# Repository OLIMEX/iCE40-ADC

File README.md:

# iCE40-ADC
Extension module for iCE40HX1K-EVB or iCE40HX8K-EVB.

Adds fast Analog-Digital-Converter (ADC) functionality to the main board.

You can effectively use up to 4 x iCE40-ADC with a single EVB board (or up to 2 x iCE40-ADC 
when you have iCE40-IO connected to the same bus).

You can use the exported PDFs to access the schematic or the bill of materials. 

We used the latest KiCad night builds to create the design. Please use a new version KiCad to open it. 

License information should be found in LICENSE.txt

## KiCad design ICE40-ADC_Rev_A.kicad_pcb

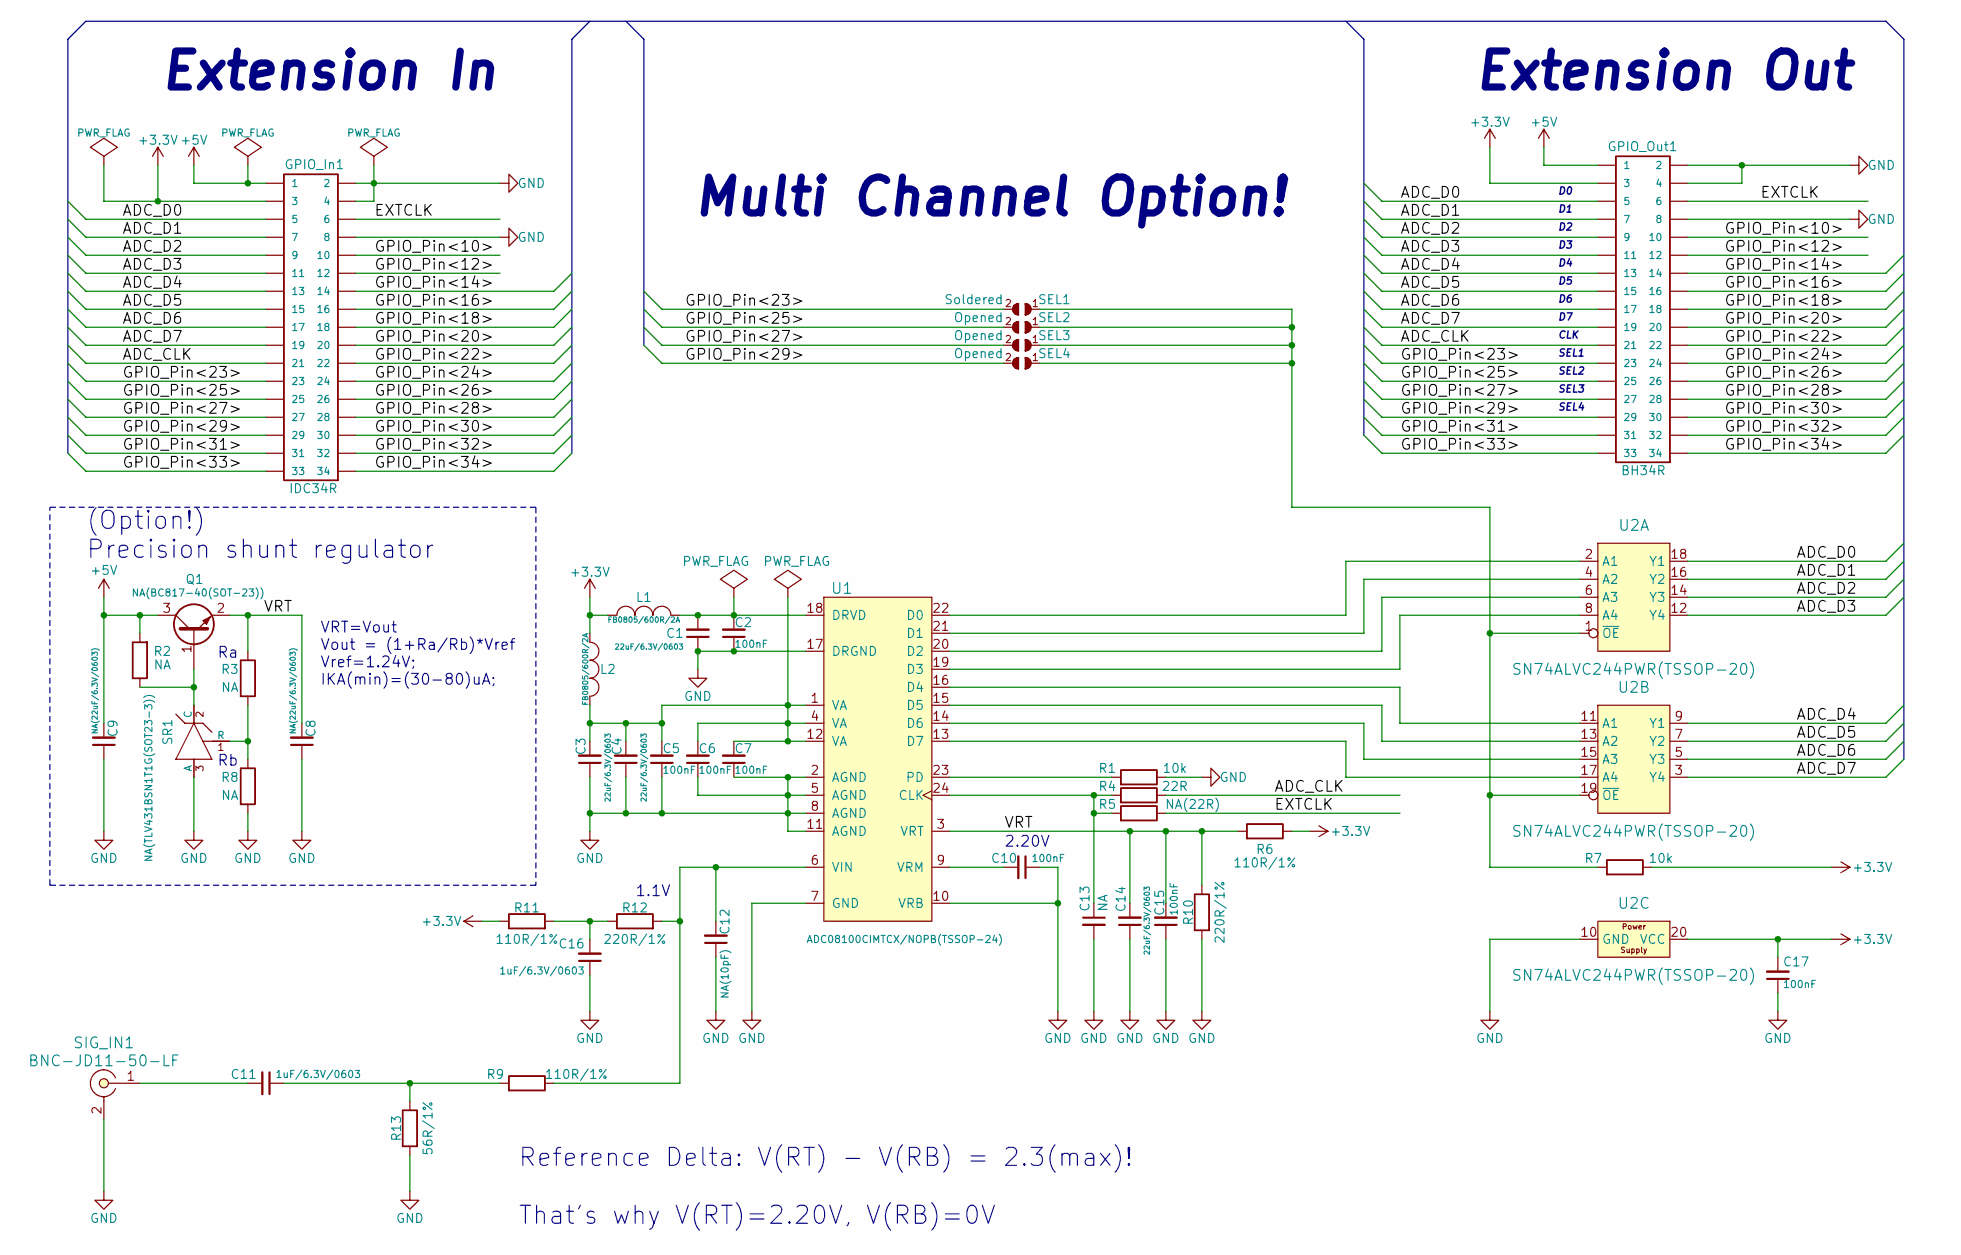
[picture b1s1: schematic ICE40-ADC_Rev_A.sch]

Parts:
C1, C3, C4, C14: 22uF/6.3V/0603; C_0603_5MIL_DWS
C2, C5, C6, C7, C10, C15, C17: 100nF; C_0402_5MIL_DWS
C8, C9: NA(22uF/6.3V/0603); C_0603_5MIL_DWS
C11, C16: 1uF/6.3V/0603; C_0603_5MIL_DWS
C12: NA(10pF); C_0402_5MIL_DWS
C13: NA; C_0402_5MIL_DWS
GPIO_In1: IDC34R; IDC34R_PCB
GPIO_Out1: BH34R
L1, L2: FB0805/600R/2A; L_0805_5MIL_DWS
Q1: NA(BC817-40(SOT-23)); SOT23
R1, R7: 10k; R_0402_5MIL_DWS
R2, R3, R8: NA; R_0402_5MIL_DWS
R4: 22R; R_0402_5MIL_DWS
R5: NA(22R); R_0402_5MIL_DWS
R6, R9, R11: 110R/1%; R_0402_5MIL_DWS
R10, R12: 220R/1%; R_0402_5MIL_DWS
R13: 56R/1%; R_0402_5MIL_DWS
SEL1: Soldered; SJ
SEL2, SEL3, SEL4: Opened; SJ
SIG_IN1: BNC-JD11-50-LF; BNC-JD11-50-LF_1-IN_2-GND
SR1: NA(TLV431BSN1T1G(SOT23-3)); SOT-23
U1: ADC08100CIMTCX/NOPB(TSSOP-24); TSSOP-24_Pitch-0.65mm_7.80x6.40x1.20mm
U2: SN74ALVC244PWR(TSSOP-20); TSSOP20_Pitch-0.65mm_6.6x4.5x1.2mm

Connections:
+3V3: C17.2, GPIO_In1.3, GPIO_Out1.3, L1.2, L2.2, R6.1, R7.1, R11.1, U2.20 (VCC)
+5V: C9.2, GPIO_In1.1, GPIO_Out1.1, Q1.3 (C), R2.2
/ADC_CLK: GPIO_In1.21, GPIO_Out1.21, R4.1
/ADC_D0: GPIO_In1.5, GPIO_Out1.5, U2.18 (Y1)
/ADC_D1: GPIO_In1.7, GPIO_Out1.7, U2.16 (Y2)
/ADC_D2: GPIO_In1.9, GPIO_Out1.9, U2.14 (Y3)
/ADC_D3: GPIO_In1.11, GPIO_Out1.11, U2.12 (Y4)
/ADC_D4: GPIO_In1.13, GPIO_Out1.13, U2.9 (Y1)
/ADC_D5: GPIO_In1.15, GPIO_Out1.15, U2.7 (Y2)
/ADC_D6: GPIO_In1.17, GPIO_Out1.17, U2.5 (Y3)
/ADC_D7: GPIO_In1.19, GPIO_Out1.19, U2.3 (Y4)
/EXTCLK: GPIO_In1.6, GPIO_Out1.6, R5.1
/GPIO_Pin<10>: GPIO_In1.10, GPIO_Out1.10
/GPIO_Pin<12>: GPIO_In1.12, GPIO_Out1.12
/GPIO_Pin<14>: GPIO_In1.14, GPIO_Out1.14
/GPIO_Pin<16>: GPIO_In1.16, GPIO_Out1.16
/GPIO_Pin<18>: GPIO_In1.18, GPIO_Out1.18
/GPIO_Pin<20>: GPIO_In1.20, GPIO_Out1.20
/GPIO_Pin<22>: GPIO_In1.22, GPIO_Out1.22
/GPIO_Pin<23>: GPIO_In1.23, GPIO_Out1.23, SEL1.2
/GPIO_Pin<24>: GPIO_In1.24, GPIO_Out1.24
/GPIO_Pin<25>: GPIO_In1.25, GPIO_Out1.25, SEL2.2
/GPIO_Pin<26>: GPIO_In1.26, GPIO_Out1.26
/GPIO_Pin<27>: GPIO_In1.27, GPIO_Out1.27, SEL3.2
/GPIO_Pin<28>: GPIO_In1.28, GPIO_Out1.28
/GPIO_Pin<29>: GPIO_In1.29, GPIO_Out1.29, SEL4.2
/GPIO_Pin<30>: GPIO_In1.30, GPIO_Out1.30
/GPIO_Pin<31>: GPIO_In1.31, GPIO_Out1.31
/GPIO_Pin<32>: GPIO_In1.32, GPIO_Out1.32
/GPIO_Pin<33>: GPIO_In1.33, GPIO_Out1.33
/GPIO_Pin<34>: GPIO_In1.34, GPIO_Out1.34
/VRT: C8.2, C14.2, C15.2, Q1.2 (E), R3.1, R6.2, R10.1, U1.3 (VRT)
GND: C1.1, C2.1, C3.1, C4.1, C5.1, C6.1, C7.1, C8.1, C9.1, C10.1, C12.1, C13.2, C14.1, C15.1, C16.1, C17.1, GPIO_In1.2, GPIO_In1.4, GPIO_In1.8, GPIO_Out1.2, GPIO_Out1.4, GPIO_Out1.8, R1.1, R8.2, R10.2, R13.2, SIG_IN1.2, SR1.3 (A), U1.2 (AGND), U1.5 (AGND), U1.7 (GND), U1.8 (AGND), U1.10 (VRB), U1.11 (AGND), U1.17 (DRGND), U2.10 (GND)
unnamed: C1.2, C2.2, L1.1, U1.18 (DRVD)
unnamed: C3.2, C4.2, C5.2, C6.2, C7.2, L2.1, U1.1 (VA), U1.4 (VA), U1.12 (VA)
unnamed: C10.2, U1.9 (VRM)
unnamed: C11.1, R9.2, R13.1
unnamed: C11.2, SIG_IN1.1
unnamed: C12.2, R9.1, R12.2, U1.6 (VIN)
unnamed: C13.1, R4.2, R5.2, U1.24 (CLK)
unnamed: C16.2, R11.2, R12.1
unnamed: Q1.1 (B), R2.1, SR1.2 (C)
unnamed: R1.2, U1.23 (PD)
unnamed: R3.2, R8.1, SR1.1 (R)
unnamed: R7.2, SEL1.1, SEL2.1, SEL3.1, SEL4.1, U2.1 (~OE), U2.19 (~OE)
unnamed: U1.13 (D7), U2.17 (A4)
unnamed: U1.14 (D6), U2.15 (A3)
unnamed: U1.15 (D5), U2.13 (A2)
unnamed: U1.16 (D4), U2.11 (A1)
unnamed: U1.19 (D3), U2.8 (A4)
unnamed: U1.20 (D2), U2.6 (A3)
unnamed: U1.21 (D1), U2.4 (A2)
unnamed: U1.22 (D0), U2.2 (A1)

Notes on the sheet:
Extension Out
Extension In
VRT=Vout Vout = (1+Ra/Rb)*Vref Vref=1.24V; IKA(min)=(30-80)uA;
2.20V
1.1V
Reference Delta: V(RT) - V(RB) = 2.3(max)! That's why V(RT)=2.20V, V(RB)=0V
(Option!) Precision shunt regulator
Multi Channel Option!
CLK
SEL1
SEL2
SEL3
SEL4

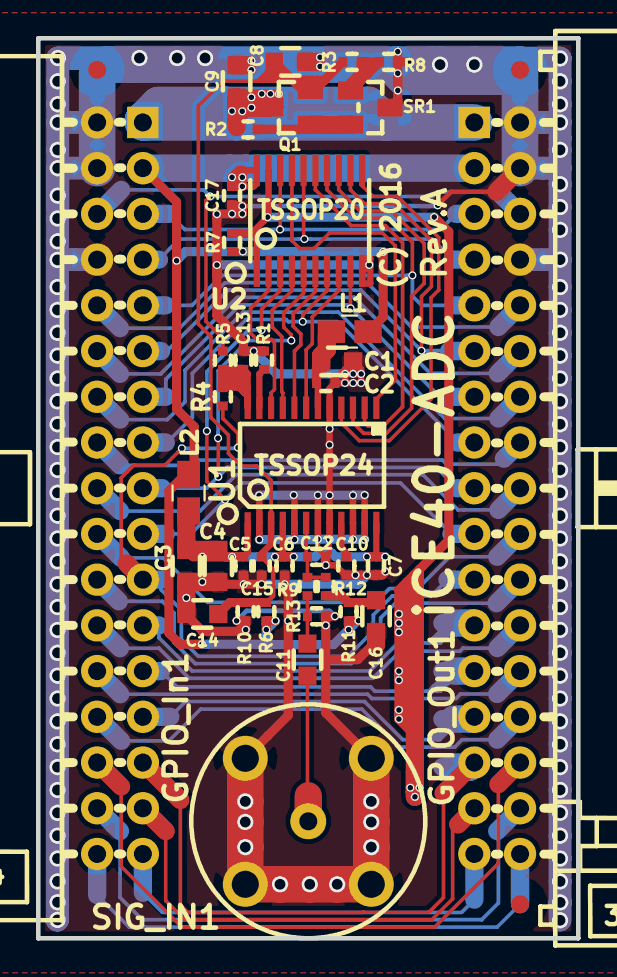
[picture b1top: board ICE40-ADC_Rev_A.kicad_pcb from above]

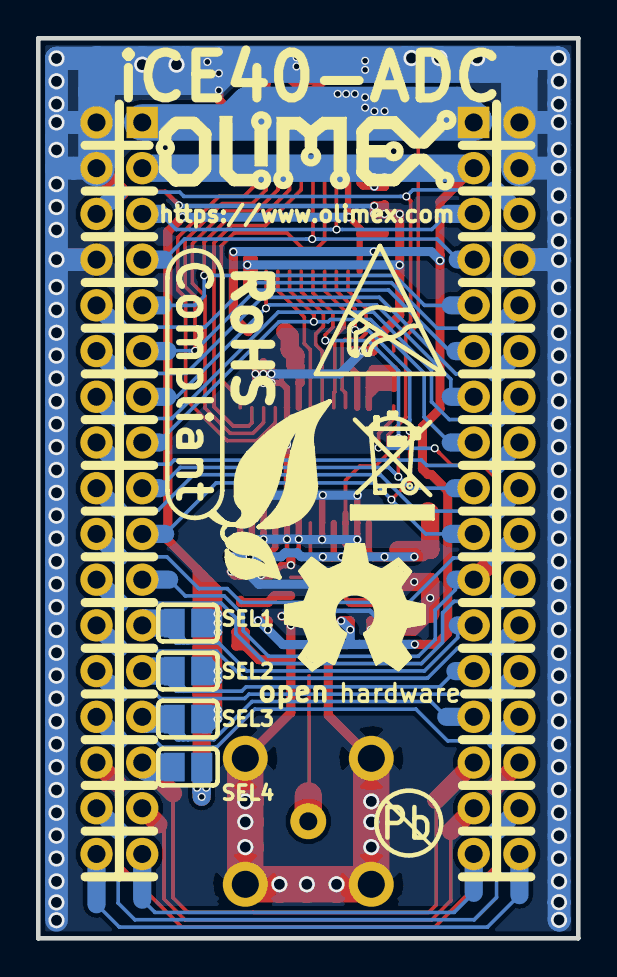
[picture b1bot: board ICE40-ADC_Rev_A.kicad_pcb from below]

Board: 2 copper layers, 30.0 x 50.0 mm, 45 parts (6 on the bottom side), 53 nets.

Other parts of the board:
Ref**: Val**; LOGO_ANTISTATIC_1
Ref**#2: Val**; LOGO_ROHS_1

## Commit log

2017-10-24 :boom::camel: Added .gitattributes

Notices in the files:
ICE40-ADC_Rev_A.kicad_pcb:
(C) 2016
